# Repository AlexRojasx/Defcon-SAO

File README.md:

# Defcon-SAO

This project is to create a simple and Fun PCB that works for Defcon as a SAO. Made this because my dad was lazy and didn't want to do it, @ElJjefeDSecurIT.

This will inclued:
  - 0.1" 2x3 connector to connect with badges and other stuff
  - Resistors
  - Right angle or back lighting LEDs
  - cool pirate

Schematic:

For the schematics, I implemented 3 LEDs, one for each of the clear parts on the PCB where there will be no soldermask, copper, or silkscreen. The resistors are marked with x as the resistances will vary depending on the LEDs used. This means that for blue LEDs there will be lower ohm resistors and for Red LEDs there will be higher ohm resistors. To calculate the resitance of the resistors, I used ohms law, V=IR, using the voltage drop I wanted over the resistor for V and the desired forward current for each LED as I. For the LEDs in parralell I simply doubled the forward current for one LED and then calculated the resistance.

Board Layout:

The circuit is quite simple so routing wasn't too difficult. There are two copper pours, one on each side that are connected to ground, and Power traces that are 0.5 mm thick. The parts were set on the back of the PCB to provide a nice finish on the front while allowing the PCB to still glow from the back.

3d Model:

As you can see, the Pirate is fully visible from the front with no traces or parts to obstruct it.

Assembly:

I ordered 165 pirates for assembly to bring to Defcon. They were assembled by hand using a reflow oven, solder paste for the SMD components, and hand soldered through hole pins.

This board is assembled with solder paste and SMD components

Placing the board in the reflow oven

Single fully soldered board

all 155 fully assembled and soldered boards, upwards of 800 SMD components and almost 1000 through hole pins.

Finalized Board:

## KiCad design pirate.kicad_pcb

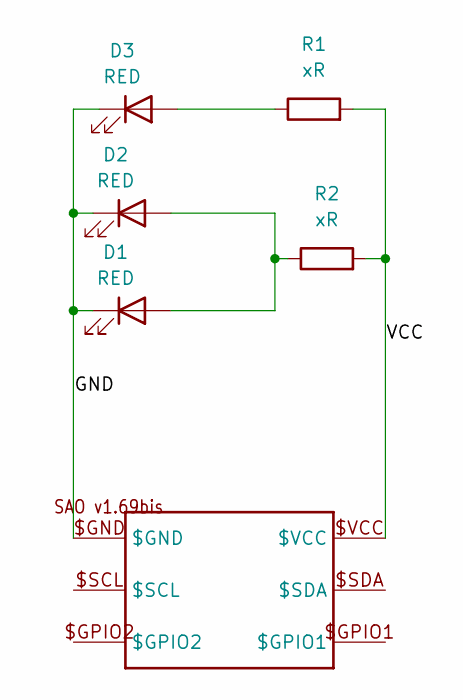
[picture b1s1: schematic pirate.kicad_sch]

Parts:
D1, D2, D3: RED; LED_0402_1005Metric
R1, R2: xR; LED_0402_1005Metric
U$1: SAO-1.69; 2X3-SHROUDED-FEMALE

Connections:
/GND: D1.1 (K), D2.1 (K), D3.1 (K), U$1.$GND
/VCC: R1.2, R2.2, U$1.$VCC
unnamed: D1.2 (A), D2.2 (A), R2.1
unnamed: D3.2 (A), R1.1

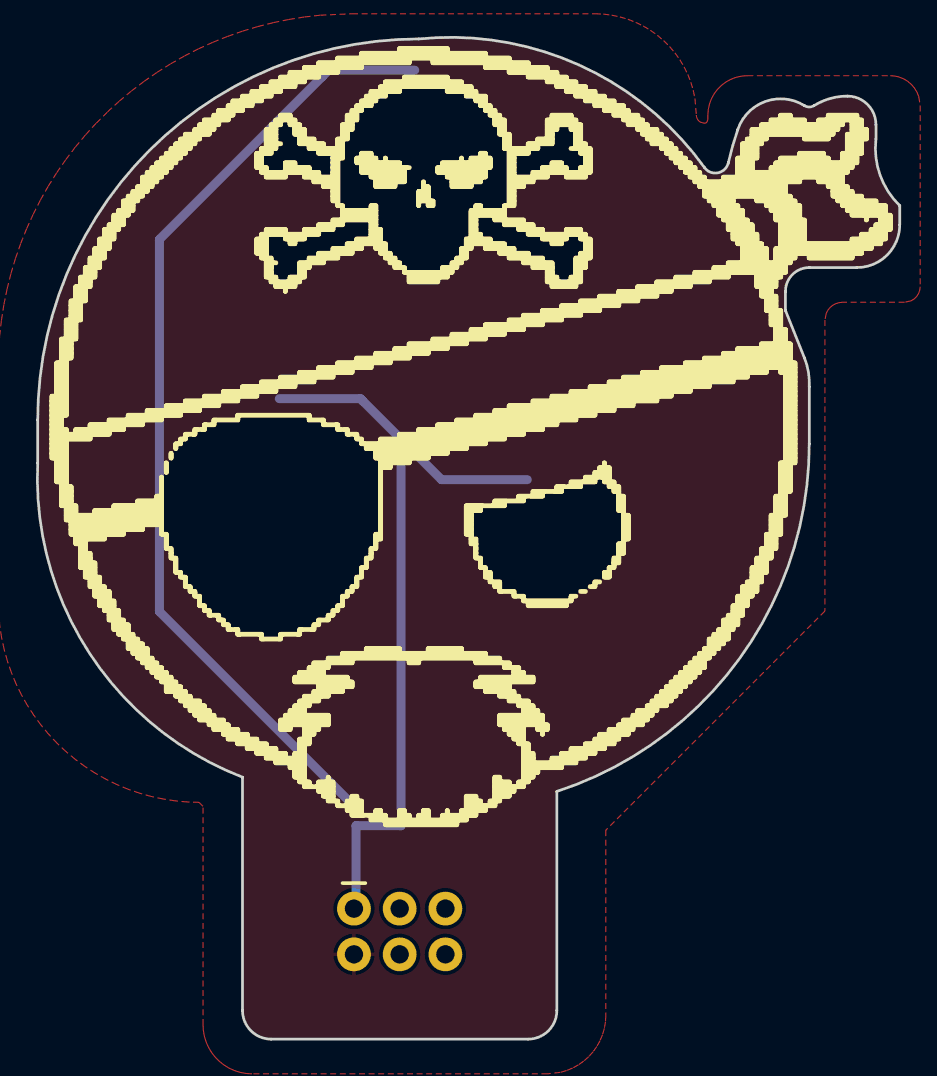
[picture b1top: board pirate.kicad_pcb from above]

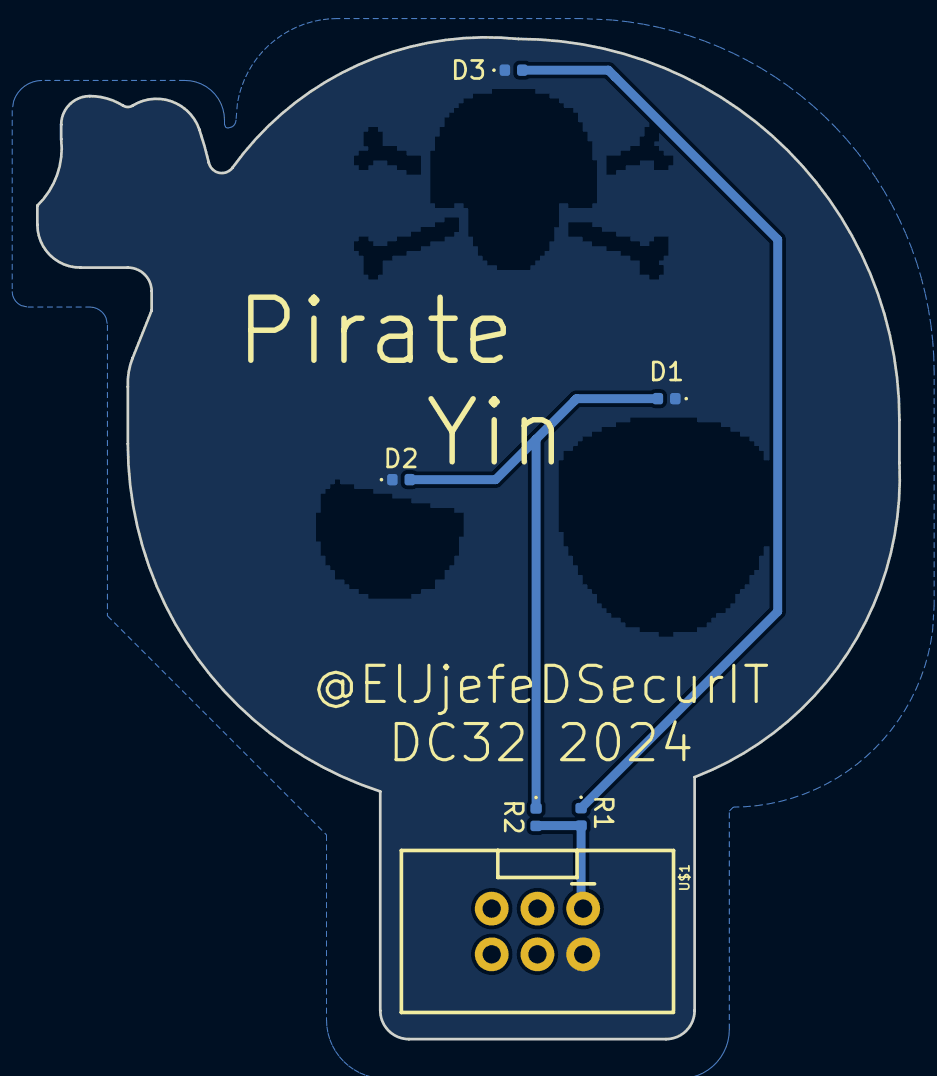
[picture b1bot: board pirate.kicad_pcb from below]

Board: 2 copper layers, 47.9 x 55.7 mm, 6 parts (5 on the bottom side), 4 nets.
